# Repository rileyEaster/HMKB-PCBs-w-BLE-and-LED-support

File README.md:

# HMBK70 PCB with BLE and LED

A PCB designed in KiCad based on the [nice!nano](https://nicekeyboards.com/nice-nano/) that enables LED and wireless functionality for custom builds that use a [HMKB70](https://heavymetalkeyboards.com/collections) chassis and MX switches. 

## Overview

This project currently contains a single schematic and PCB file. Currently, there is only support for 3V monochromatic LEDs. Wireless functionality has not yet been addressed. An unconventional layout, which uses 4 and 3 keys on the left and right of the space bar respectively, has been implemented. 

## Features

- Key switch matrix connected to the micro controller
- Footprints with holes for MX switches and 3mm, 3v LEDs
- Easy to adapt for other layouts or microcontrollers

## Project Files

- `HMKB70_Nicenano_LED.kicad_pro` — KiCad project file
- `HMKB70_Nicenano_LED.kicad_sch` — schematic file
- `kHMKB70_Nicenano_LED.kicad_pcb` — PCB layout file

## Status

- [x] Schematic for monochromatic LEDs
- [x] PCB precise layout
- [ ] Designs for solder mask
- [ ] Battery integration
- [ ] Wireless Functionality

## Intended Additions

- Full spectrum, adjustable RGB
- CAD models of the HMKB70 integrated into KiCad's 3D viewer

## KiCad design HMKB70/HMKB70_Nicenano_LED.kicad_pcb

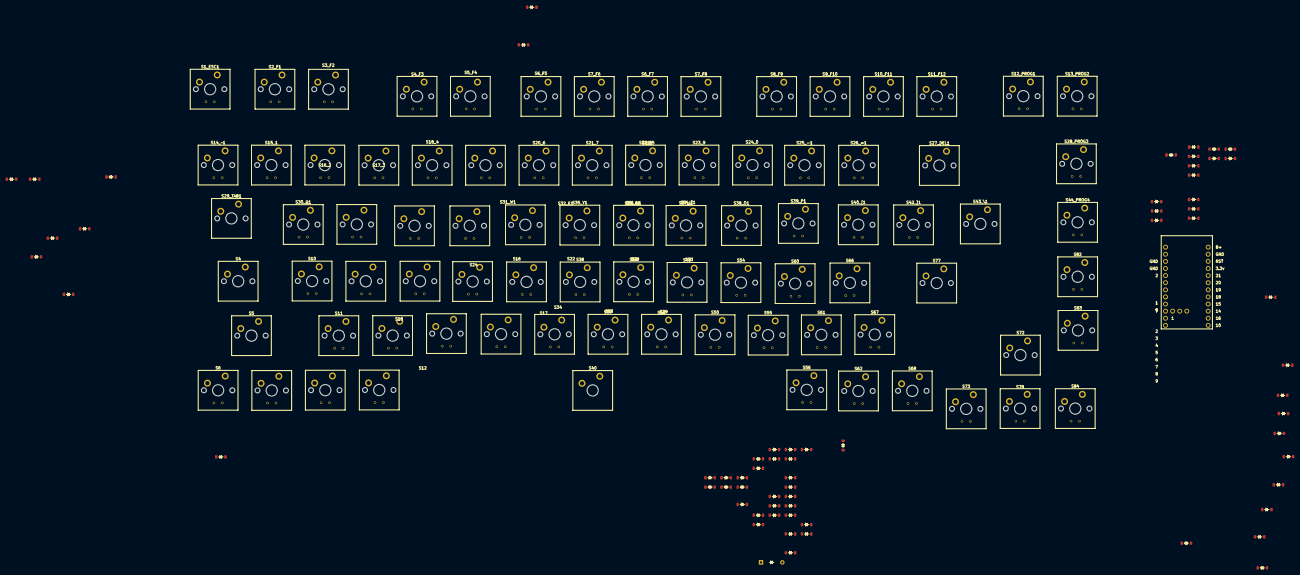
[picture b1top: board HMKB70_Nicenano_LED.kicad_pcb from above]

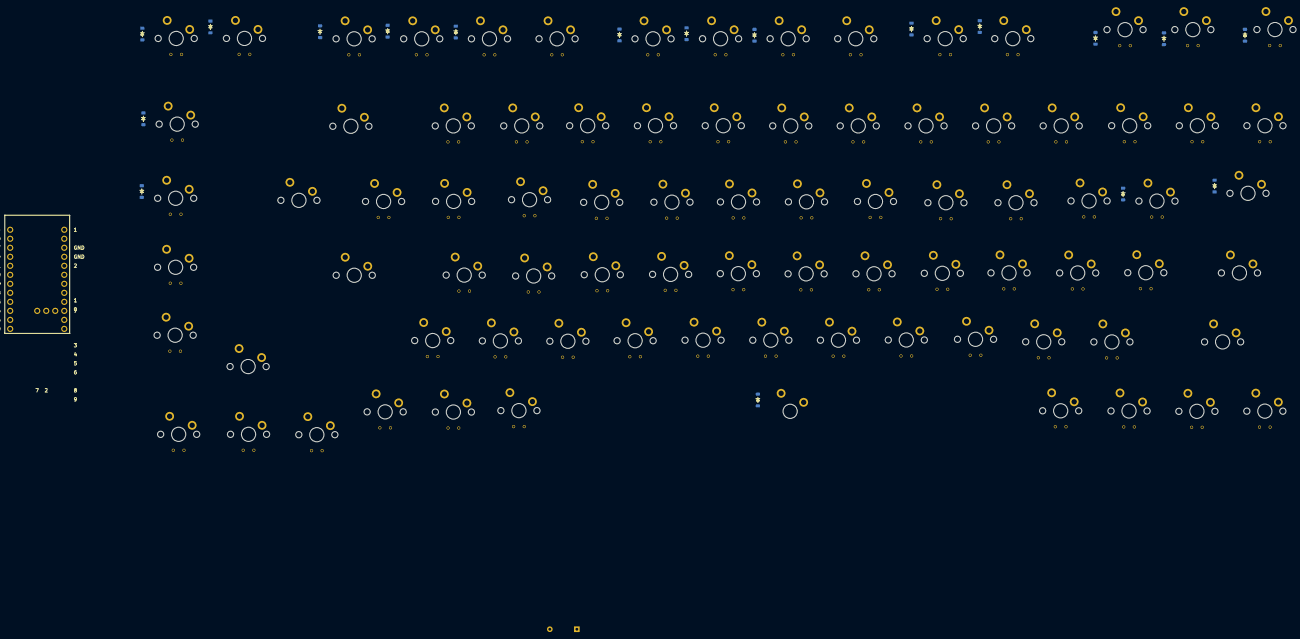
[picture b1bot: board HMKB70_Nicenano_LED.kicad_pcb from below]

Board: 2 copper layers, 169 parts (18 on the bottom side), 101 nets, no tracks yet.

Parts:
D1_ESC1, D2, D2_F1, D3_F2, D4, D4_F3, D5, D5_F4, D6, D6_F5, D6_F7, D7_F6, D7_F8, D8, D8_F9, D9_F10, D10, D10_F11, D11, D11_F12, D12, D12_PROG1, D13_PROG2, D14, D16, D17, D18, D20, D22, D23, D24, D26, D28, D28_PROG3, D29, D29_TAB1, D30_Q1, D31, D31_W1, D32_E1, D33, D33_R1, D34, D34_T1, D35_Y1, D36, D36_U1, D37_I1, D38, D38_O1, D39, D39_P1, D40, D40_[1, D42, D43_\1, D43_\2, D44, D44_PROG4, D45, D47, D49, D50, D52, D54, D55, D56, D58, D60, D61, D62, D64, D66, D67, D68, D70, D72, D73, D75, D78, D82, D83, D84: Diode_SOD-123
D77: Diode_DO-35
S1_ESC1, S2_F1, S3_F2, S4_F3, S5_F4, S6, S6_F5, S6_F7, S7_F6, S7_F8, S8_F9, S9_F10, S10, S10_F11, S11, S11_F12, S12, S12_PROG1, S13_PROG2, S14_~1, S15_1, S16, S16_2, S17, S17_3, S18, S18_4, S19_5, S20_6, S21_7, S22, S22_8, S23, S23_9, S24, S24_0, S25_-1, S26_=1, S28, S28_PROG3, S29, S30_Q1, S31_W1, S32_E1, S33, S33_R1, S34, S34_T1, S35_Y1, S36_U1, S37_I1, S38, S38_O1, S39, S39_P1, S40_[1, S42_]1, S44, S44_PROG4, S45, S49, S50, S54, S55, S56, S60, S61, S62, S66, S67, S68, S73, S78, S82, S83, S84: MX_PCB_1.00u
S4: MX_PCB_1.75u
S5, S77: MX_PCB_2.25u
S27_DEL1: MX_PCB_2.00u
S29_TAB1, S43_\1, S72: MX_PCB_1.50u
S40: MX_Plate_7.00u
U1: Nice_Nano_V2

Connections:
Col 0: S1_ESC1.1, S2_F1.1, S4.1, S5.1, S6.1, S10.1, S11.1, S12.1, S14_~1.1, S15_1.1, S29_TAB1.1, S30_Q1.1, U1.2 (0)
Col 1: S3_F2.1, S4_F3.1, S16.1, S16_2.1, S17.1, S17_3.1, S18.1, S22.1, S23.1, S24.1, S31_W1.1, S32_E1.1, U1.1
Col 2: S5_F4.1, S6_F5.1, S18_4.1, S19_5.1, S28.1, S29.1, S33.1, S33_R1.1, S34.1, S34_T1.1, U1.5 (2)
Col 3: S6_F7.1, S7_F6.1, S20_6.1, S21_7.1, S35_Y1.1, S36_U1.1, S38.1, S39.1, S40.1, S44.1, S45.1, U1.6 (3)
Col 4: S7_F8.1, S8_F9.1, S22_8.1, S23_9.1, S37_I1.1, S38_O1.1, S49.1, S50.1, S54.1, S55.1, S56.1, U1.7 (4)
Col 5: S9_F10.1, S10_F11.1, S24_0.1, S25_-1.1, S39_P1.1, S40_[1.1, S60.1, S61.1, S62.1, S66.1, S67.1, S68.1, U1.8 (5)
Col 6: S11_F12.1, S12_PROG1.1, S26_=1.1, S27_DEL1.1, S42_]1.1, S43_\1.1, S72.1, S73.1, S77.1, S78.1, U1.9 (6)
Col 7: S13_PROG2.1, S28_PROG3.1, S44_PROG4.1, S82.1, S83.1, S84.1, U1.10 (7)
unnamed: D1_ESC1.2 (A), S1_ESC1.2
unnamed: D2.2 (A), S14_~1.2
unnamed: D2_F1.2 (A), S2_F1.2
unnamed: D3_F2.2 (A), S3_F2.2
unnamed: D4.2 (A), S4.2
unnamed: D4_F3.2 (A), S4_F3.2
unnamed: D5.2 (A), S5.2
unnamed: D5_F4.2 (A), S5_F4.2
unnamed: D6.2 (A), S6.2
unnamed: D6_F5.2 (A), S6_F5.2
unnamed: D6_F7.2 (A), S6_F7.2
unnamed: D7_F6.2 (A), S7_F6.2
unnamed: D7_F8.2 (A), S7_F8.2
unnamed: D8.2 (A), S15_1.2
unnamed: D8_F9.2 (A), S8_F9.2
unnamed: D9_F10.2 (A), S9_F10.2
unnamed: D10.2 (A), S10.2
unnamed: D10_F11.2 (A), S10_F11.2
unnamed: D11.2 (A), S11.2
unnamed: D11_F12.2 (A), S11_F12.2
unnamed: D12.2 (A), S12.2
unnamed: D12_PROG1.2 (A), S12_PROG1.2
unnamed: D13_PROG2.2 (A), S13_PROG2.2
unnamed: D14.2 (A), S16_2.2
unnamed: D16.2 (A), S16.2
unnamed: D17.2 (A), S17.2
unnamed: D18.2 (A), S18.2
unnamed: D20.2 (A), S17_3.2
unnamed: D22.2 (A), S22.2
unnamed: D23.2 (A), S23.2
unnamed: D24.2 (A), S24.2
unnamed: D26.2 (A), S18_4.2
unnamed: D28.2 (A), S28.2
unnamed: D28_PROG3.2 (A), S28_PROG3.2
unnamed: D29.2 (A), S29.2
unnamed: D29_TAB1.2 (A), S29_TAB1.2
unnamed: D30_Q1.2 (A), S30_Q1.2
unnamed: D31.2 (A), S19_5.2
unnamed: D31_W1.2 (A), S31_W1.2
unnamed: D32_E1.2 (A), S32_E1.2
unnamed: D33.2 (A), S33.2
unnamed: D33_R1.2 (A), S33_R1.2
unnamed: D34.2 (A), S34.2
unnamed: D34_T1.2 (A), S34_T1.2
unnamed: D35_Y1.2 (A), S35_Y1.2
unnamed: D36.2 (A), S20_6.2
unnamed: D36_U1.2 (A), S36_U1.2
unnamed: D37_I1.2 (A), S37_I1.2
unnamed: D38.2 (A), S38.2
unnamed: D38_O1.2 (A), S38_O1.2
unnamed: D39.2 (A), S39.2
unnamed: D39_P1.2 (A), S39_P1.2
unnamed: D40.2 (A), S40.2
unnamed: D40_[1.2 (A), S40_[1.2
unnamed: D42.2 (A), S21_7.2
unnamed: D43_\1.2 (A), S42_]1.2
unnamed: D43_\2.2 (A), S43_\1.2
unnamed: D44.2 (A), S44.2
unnamed: D44_PROG4.2 (A), S44_PROG4.2
unnamed: D45.2 (A), S45.2
unnamed: D47.2 (A), S22_8.2
unnamed: D49.2 (A), S49.2
unnamed: D50.2 (A), S50.2
unnamed: D52.2 (A), S23_9.2
unnamed: D54.2 (A), S54.2
unnamed: D55.2 (A), S55.2
unnamed: D56.2 (A), S56.2
unnamed: D58.2 (A), S24_0.2
unnamed: D60.2 (A), S60.2
unnamed: D61.2 (A), S61.2
unnamed: D62.2 (A), S62.2
unnamed: D64.2 (A), S25_-1.2
unnamed: D66.2 (A), S66.2
unnamed: D67.2 (A), S67.2
unnamed: D68.2 (A), S68.2
unnamed: D70.2 (A), S26_=1.2
unnamed: D72.2 (A), S72.2
unnamed: D73.2 (A), S73.2
unnamed: D75.2 (A), S27_DEL1.2
unnamed: D77.2 (A), S77.2
unnamed: D78.2 (A), S78.2
unnamed: D82.2 (A), S82.2
unnamed: D83.2 (A), S83.2
unnamed: D84.2 (A), S84.2
Row 0: D1_ESC1.1 (K), D2_F1.1 (K), D3_F2.1 (K), D4_F3.1 (K), D5_F4.1 (K), D6_F5.1 (K), D6_F7.1 (K), D7_F6.1 (K), D7_F8.1 (K), D8_F9.1 (K), D9_F10.1 (K), D10_F11.1 (K), D11_F12.1 (K), D12_PROG1.1 (K), D13_PROG2.1 (K), U1.11 (8)
Row 1: D2.1 (K), D8.1 (K), D14.1 (K), D20.1 (K), D26.1 (K), D28_PROG3.1 (K), D31.1 (K), D36.1 (K), D42.1 (K), D47.1 (K), D52.1 (K), D58.1 (K), D64.1 (K), D70.1 (K), D75.1 (K), U1.12 (9)
Row 2-1: D29_TAB1.1 (K), D31_W1.1 (K), D33_R1.1 (K), D35_Y1.1 (K), D37_I1.1 (K), D39_P1.1 (K), D43_\1.1 (K), D44_PROG4.1 (K), U1.19 (20)
Row 2-2: D30_Q1.1 (K), D32_E1.1 (K), D34_T1.1 (K), D36_U1.1 (K), D38_O1.1 (K), D40_[1.1 (K), D43_\2.1 (K), U1.20 (21)
Row 3-1: D4.1 (K), D16.1 (K), D28.1 (K), D38.1 (K), D49.1 (K), D60.1 (K), D82.1 (K), U1.17 (18)
Row 3-2: D10.1 (K), D22.1 (K), D33.1 (K), D44.1 (K), D54.1 (K), D66.1 (K), D77.1 (K), U1.18 (19)
Row 4-1: D11.1 (K), D23.1 (K), D34.1 (K), D45.1 (K), D55.1 (K), D67.1 (K), D83.1 (K), U1.15 (14)
Row 4-2: D5.1 (K), D17.1 (K), D29.1 (K), D39.1 (K), D50.1 (K), D61.1 (K), D72.1 (K), U1.16 (15)
Row 5-1: D6.1 (K), D12.1 (K), D18.1 (K), D24.1 (K), D40.1 (K), D56.1 (K), D62.1 (K), D68.1 (K), D73.1 (K), D78.1 (K), D84.1 (K), U1.13 (10), U1.14 (16)

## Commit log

2026-04-18 Myriad fixes
    Organized Repo, added LEDs and footprints, copied estimated size prior PCB, Resized keycaps to 18mm, etc
2026-04-20 First README
    Drafted a README with standard details
2026-04-20 Cherry typo fix
    Replaced Cherry with MX and cleaned up some phrasing.
2026-04-20 1u footprint fix and misc other
    Fixed 1u MX switch footprint, changed LED line to an ugly magenta, fixed LED circuit with current drain.
